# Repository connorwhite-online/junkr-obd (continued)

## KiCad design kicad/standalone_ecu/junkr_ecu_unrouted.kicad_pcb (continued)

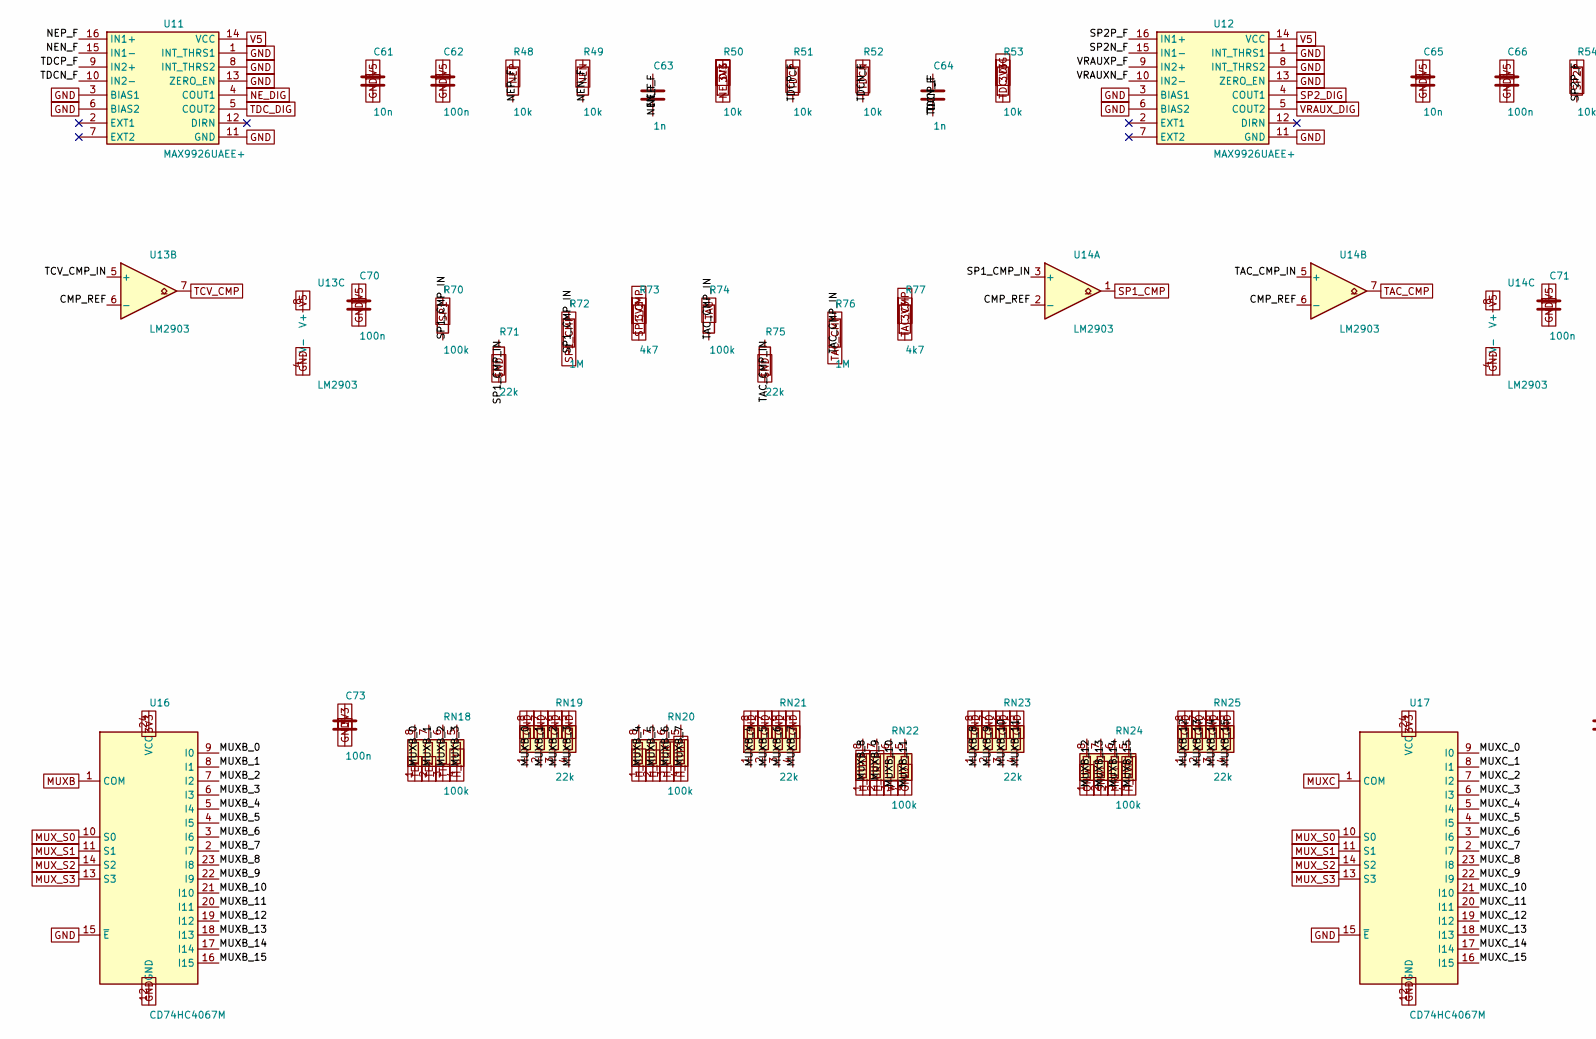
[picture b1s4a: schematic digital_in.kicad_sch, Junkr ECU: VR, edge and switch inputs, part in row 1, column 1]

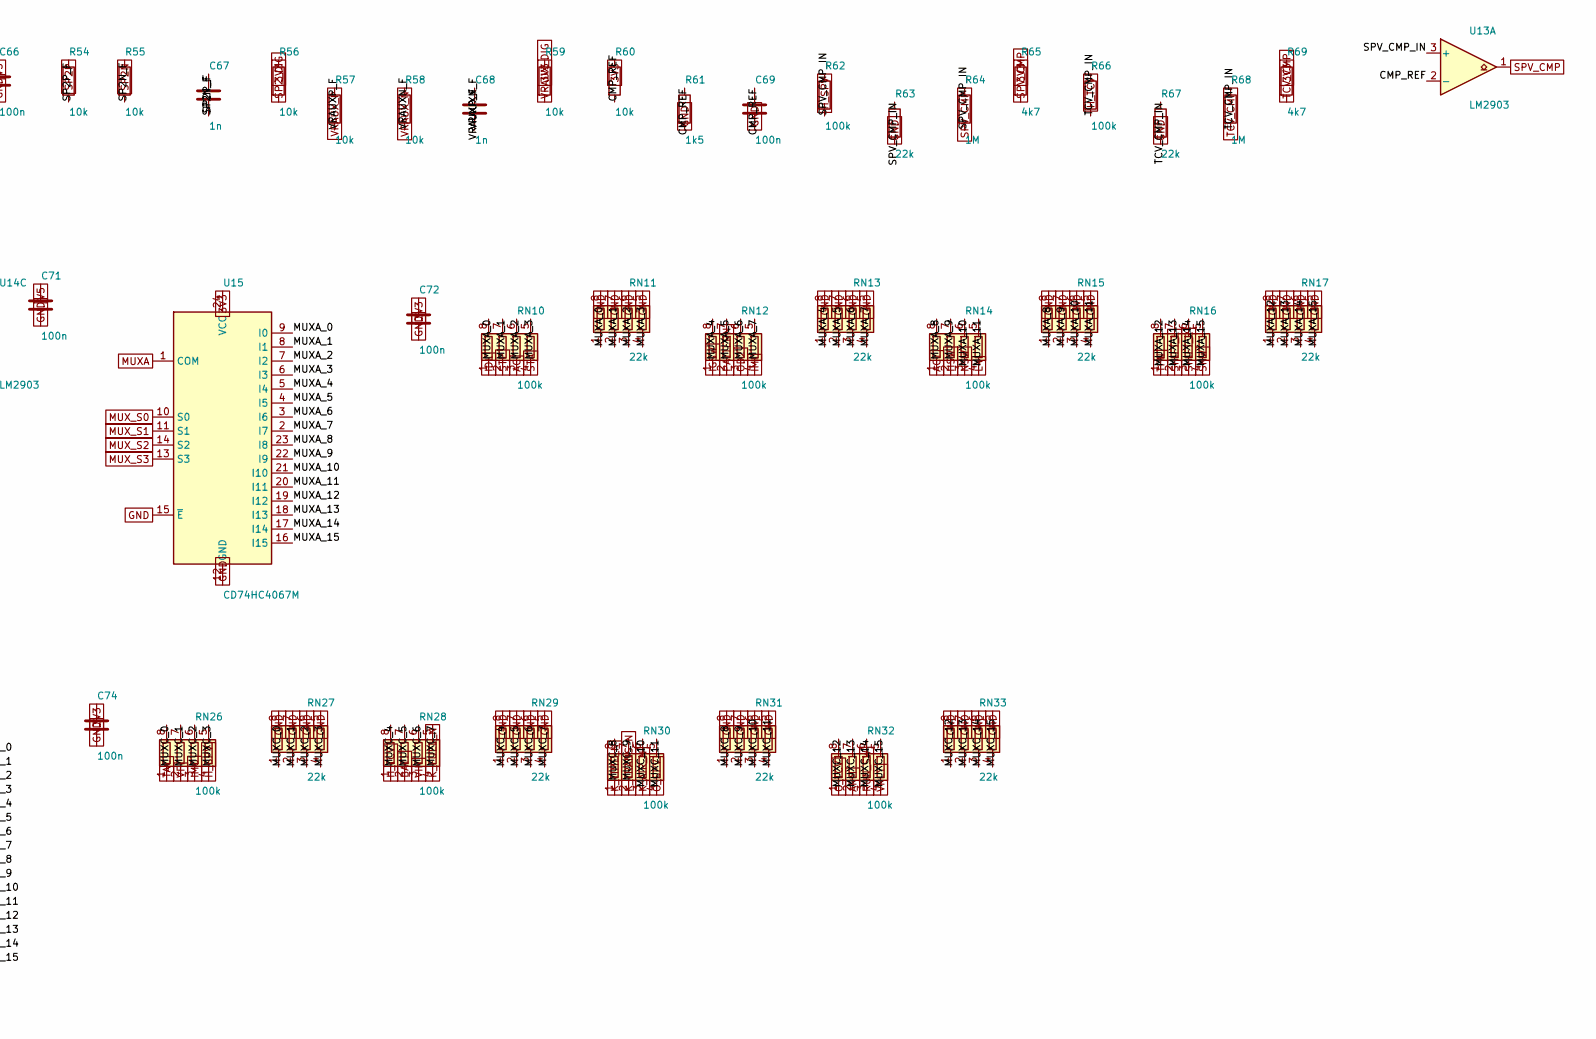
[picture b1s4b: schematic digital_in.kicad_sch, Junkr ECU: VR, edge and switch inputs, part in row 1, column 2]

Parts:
C61, C65: 10n; C_0603_1608Metric
C62, C66, C69, C70, C71, C72, C73, C74: 100n; C_0603_1608Metric
C63, C64, C67, C68: 1n; C_0603_1608Metric
R48, R49, R50, R51, R52, R53, R54, R55, R56, R57, R58, R59, R60: 10k; R_0603_1608Metric
R61: 1k5; R_0603_1608Metric
R62, R66, R70, R74: 100k; R_0603_1608Metric
R63, R67, R71, R75: 22k; R_0603_1608Metric
R64, R68, R72, R76: 1M; R_0603_1608Metric
R65, R69, R73, R77: 4k7; R_0603_1608Metric
RN10, RN12, RN14, RN16, RN18, RN20, RN22, RN24, RN26, RN28, RN30, RN32: 100k; R_Array_Convex_4x0603
RN11, RN13, RN15, RN17, RN19, RN21, RN23, RN25, RN27, RN29, RN31, RN33: 22k; R_Array_Convex_4x0603
U11, U12: MAX9926UAEE+; QSOP-16_3.9x4.9mm_P0.635mm; MPN MAX9926UAEE+
U13, U14: LM2903; SOIC-8_3.9x4.9mm_P1.27mm; MPN LM2903DR
U15, U16, U17: CD74HC4067M; SOIC-24W_7.5x15.4mm_P1.27mm; MPN CD74HC4067M96

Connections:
3V3: C72.1, C73.1, C74.1, R50.1, R53.1, R56.1, R59.1, R60.1, R65.1, R69.1, R73.1, R77.1, U15.24 (VCC), U16.24 (VCC), U17.24 (VCC); also elsewhere on the board
AC: RN10.3 (R3.1); also elsewhere on the board
ACT: RN14.1 (R1.1); also elsewhere on the board
ARM: RN32.2 (R2.1); also elsewhere on the board
BATT: RN28.2 (R2.1); also elsewhere on the board
CMP_REF: C69.1, R60.2, R61.1, U13.2 (-), U13.6 (-), U14.2 (-), U14.6 (-)
GIND: RN22.4 (R4.1); also elsewhere on the board
GND: C61.2, C62.2, C65.2, C66.2, C69.2, C70.2, C71.2, C72.2, C73.2, C74.2, R61.2, R63.2, R67.2, R71.2, R75.2, RN11.5 (R4.2), RN11.6 (R3.2), RN11.7 (R2.2), RN11.8 (R1.2), RN13.5 (R4.2), RN13.6 (R3.2), RN13.7 (R2.2), RN13.8 (R1.2), RN15.5 (R4.2), RN15.6 (R3.2), RN15.7 (R2.2), RN15.8 (R1.2), RN17.5 (R4.2), RN17.6 (R3.2), RN17.7 (R2.2), RN17.8 (R1.2), RN19.5 (R4.2), RN19.6 (R3.2), RN19.7 (R2.2), RN19.8 (R1.2), RN21.5 (R4.2), RN21.6 (R3.2), RN21.7 (R2.2), RN21.8 (R1.2), RN23.5 (R4.2), RN23.6 (R3.2), RN23.7 (R2.2), RN23.8 (R1.2), RN25.5 (R4.2), RN25.6 (R3.2), RN25.7 (R2.2), RN25.8 (R1.2), RN27.5 (R4.2), RN27.6 (R3.2), RN27.7 (R2.2), RN27.8 (R1.2), RN29.5 (R4.2), RN29.6 (R3.2), RN29.7 (R2.2), RN29.8 (R1.2), RN31.5 (R4.2), RN31.6 (R3.2), RN31.7 (R2.2), RN31.8 (R1.2), RN33.5 (R4.2), RN33.6 (R3.2), RN33.7 (R2.2), RN33.8 (R1.2), U11.1 (INT_THRS1), U11.3 (BIAS1), U11.6 (BIAS2), U11.8 (INT_THRS2), U11.11 (GND), U11.13 (ZERO_EN), U12.1 (INT_THRS1), U12.3 (BIAS1), U12.6 (BIAS2), U12.8 (INT_THRS2), U12.11 (GND), U12.13 (ZERO_EN), U13.4 (V-), U14.4 (V-), U15.12 (GND), U15.15 (~E), U16.12 (GND), U16.15 (~E), U17.12 (GND), U17.15 (~E); also elsewhere on the board
HSW: RN14.2 (R2.1); also elsewhere on the board
H_EGR: RN20.3 (R3.1); also elsewhere on the board
H_S1: RN18.4 (R4.1); also elsewhere on the board
H_S2: RN20.1 (R1.1); also elsewhere on the board
H_SL: RN20.2 (R2.1); also elsewhere on the board
H_SPV: R62.1, RN26.4 (R4.1); also elsewhere on the board
H_SREL: RN22.2 (R2.1); also elsewhere on the board
H_STH1: RN20.4 (R4.1); also elsewhere on the board
H_STH2: RN22.1 (R1.1); also elsewhere on the board
H_SVR: RN24.4 (R4.1); also elsewhere on the board
H_TCV: R66.1, RN28.1 (R1.1); also elsewhere on the board
IDL: RN10.1 (R1.1); also elsewhere on the board
IGSW: RN12.1 (R1.1); also elsewhere on the board
IMI: RN12.4 (R4.1); also elsewhere on the board
IMO: RN26.3 (R3.1); also elsewhere on the board
K_AIR_N: RN30.3 (R3.1); also elsewhere on the board
K_FUEL_N: RN28.4 (R4.1); also elsewhere on the board
K_TIME_N: RN30.1 (R1.1); also elsewhere on the board
K_TRANS_N: RN30.2 (R2.1); also elsewhere on the board
L4: RN14.4 (R4.1); also elsewhere on the board
MREL: RN24.3 (R3.1); also elsewhere on the board
MUXA: U15.1 (COM); also elsewhere on the board
MUXA_0: RN10.8 (R1.2), RN11.1 (R1.1), U15.9 (I0)
MUXA_1: RN10.7 (R2.2), RN11.2 (R2.1), U15.8 (I1)
MUXA_2: RN10.6 (R3.2), RN11.3 (R3.1), U15.7 (I2)
MUXA_3: RN10.5 (R4.2), RN11.4 (R4.1), U15.6 (I3)
MUXA_4: RN12.8 (R1.2), RN13.1 (R1.1), U15.5 (I4)
MUXA_5: RN12.7 (R2.2), RN13.2 (R2.1), U15.4 (I5)
MUXA_6: RN12.6 (R3.2), RN13.3 (R3.1), U15.3 (I6)
MUXA_7: RN12.5 (R4.2), RN13.4 (R4.1), U15.2 (I7)
MUXA_8: RN14.8 (R1.2), RN15.1 (R1.1), U15.23 (I8)
MUXA_9: RN14.7 (R2.2), RN15.2 (R2.1), U15.22 (I9)
MUXA_10: RN14.6 (R3.2), RN15.3 (R3.1), U15.21 (I10)
MUXA_11: RN14.5 (R4.2), RN15.4 (R4.1), U15.20 (I11)
MUXA_12: RN16.8 (R1.2), RN17.1 (R1.1), U15.19 (I12)
MUXA_13: RN16.7 (R2.2), RN17.2 (R2.1), U15.18 (I13)
MUXA_14: RN16.6 (R3.2), RN17.3 (R3.1), U15.17 (I14)
MUXA_15: RN16.5 (R4.2), RN17.4 (R4.1), U15.16 (I15)
MUXB: U16.1 (COM); also elsewhere on the board
MUXB_0: RN18.8 (R1.2), RN19.1 (R1.1), U16.9 (I0)
MUXB_1: RN18.7 (R2.2), RN19.2 (R2.1), U16.8 (I1)
MUXB_2: RN18.6 (R3.2), RN19.3 (R3.1), U16.7 (I2)
MUXB_3: RN18.5 (R4.2), RN19.4 (R4.1), U16.6 (I3)
MUXB_4: RN20.8 (R1.2), RN21.1 (R1.1), U16.5 (I4)
MUXB_5: RN20.7 (R2.2), RN21.2 (R2.1), U16.4 (I5)
MUXB_6: RN20.6 (R3.2), RN21.3 (R3.1), U16.3 (I6)
MUXB_7: RN20.5 (R4.2), RN21.4 (R4.1), U16.2 (I7)
MUXB_8: RN22.8 (R1.2), RN23.1 (R1.1), U16.23 (I8)
MUXB_9: RN22.7 (R2.2), RN23.2 (R2.1), U16.22 (I9)
MUXB_10: RN22.6 (R3.2), RN23.3 (R3.1), U16.21 (I10)
MUXB_11: RN22.5 (R4.2), RN23.4 (R4.1), U16.20 (I11)
MUXB_12: RN24.8 (R1.2), RN25.1 (R1.1), U16.19 (I12)
MUXB_13: RN24.7 (R2.2), RN25.2 (R2.1), U16.18 (I13)
MUXB_14: RN24.6 (R3.2), RN25.3 (R3.1), U16.17 (I14)
MUXB_15: RN24.5 (R4.2), RN25.4 (R4.1), U16.16 (I15)
MUXC: U17.1 (COM); also elsewhere on the board
MUXC_0: RN26.8 (R1.2), RN27.1 (R1.1), U17.9 (I0)
MUXC_1: RN26.7 (R2.2), RN27.2 (R2.1), U17.8 (I1)
MUXC_2: RN26.6 (R3.2), RN27.3 (R3.1), U17.7 (I2)
MUXC_3: RN26.5 (R4.2), RN27.4 (R4.1), U17.6 (I3)
MUXC_4: RN28.8 (R1.2), RN29.1 (R1.1), U17.5 (I4)
MUXC_5: RN28.7 (R2.2), RN29.2 (R2.1), U17.4 (I5)
MUXC_6: RN28.6 (R3.2), RN29.3 (R3.1), U17.3 (I6)
MUXC_7: RN28.5 (R4.2), RN29.4 (R4.1), U17.2 (I7)
MUXC_8: RN30.8 (R1.2), RN31.1 (R1.1), U17.23 (I8)
MUXC_9: RN30.7 (R2.2), RN31.2 (R2.1), U17.22 (I9)
MUXC_10: RN30.6 (R3.2), RN31.3 (R3.1), U17.21 (I10)
MUXC_11: RN30.5 (R4.2), RN31.4 (R4.1), U17.20 (I11)
MUXC_12: RN32.8 (R1.2), RN33.1 (R1.1), U17.19 (I12)
MUXC_13: RN32.7 (R2.2), RN33.2 (R2.1), U17.18 (I13)
MUXC_14: RN32.6 (R3.2), RN33.3 (R3.1), U17.17 (I14)
MUXC_15: RN32.5 (R4.2), RN33.4 (R4.1), U17.16 (I15)
MUX_S0: U15.10 (S0), U16.10 (S0), U17.10 (S0); also elsewhere on the board
MUX_S1: U15.11 (S1), U16.11 (S1), U17.11 (S1); also elsewhere on the board
MUX_S2: U15.14 (S2), U16.14 (S2), U17.14 (S2); also elsewhere on the board
MUX_S3: U15.13 (S3), U16.13 (S3), U17.13 (S3); also elsewhere on the board
NEN: R49.1; also elsewhere on the board
NEN_F: C63.2, R49.2, U11.15 (IN1-)
NEP: R48.1; also elsewhere on the board
NEP_F: C63.1, R48.2, U11.16 (IN1+)
NE_DIG: R50.2, U11.4 (COUT1); also elsewhere on the board
NSW: RN14.3 (R3.1); also elsewhere on the board
OD2: RN12.3 (R3.1); also elsewhere on the board
OILW: RN24.1 (R1.1); also elsewhere on the board
O_SPV: RN30.4 (R4.1); also elsewhere on the board
O_TCV: RN32.1 (R1.1); also elsewhere on the board
PATTERN: RN12.2 (R2.1); also elsewhere on the board
RUN_SW: RN32.3 (R3.1); also elsewhere on the board
SHIFT_2: RN16.3 (R3.1); also elsewhere on the board
SHIFT_L: RN16.2 (R2.1); also elsewhere on the board
SNW: RN16.4 (R4.1); also elsewhere on the board
SNWL: RN24.2 (R2.1); also elsewhere on the board
SP1: R70.1; also elsewhere on the board
SP1_CMP: R72.1, R73.2, U14.1; also elsewhere on the board
SP1_CMP_IN: R70.2, R71.1, R72.2, U14.3 (+)
SP2N: R55.1; also elsewhere on the board
SP2N_F: C67.2, R55.2, U12.15 (IN1-)
SP2P: R54.1; also elsewhere on the board
SP2P_F: C67.1, R54.2, U12.16 (IN1+)
SP2_DIG: R56.2, U12.4 (COUT1); also elsewhere on the board
SPV_CMP: R64.1, R65.2, U13.1; also elsewhere on the board
SPV_CMP_IN: R62.2, R63.1, R64.2, U13.3 (+)
STA: RN10.4 (R4.1); also elsewhere on the board
STP: RN10.2 (R2.1); also elsewhere on the board
TAC: R74.1, RN26.1 (R1.1); also elsewhere on the board
TAC_CMP: R76.1, R77.2, U14.7; also elsewhere on the board
TAC_CMP_IN: R74.2, R75.1, R76.2, U14.5 (+)
TCV_CMP: R68.1, R69.2, U13.7; also elsewhere on the board
TCV_CMP_IN: R66.2, R67.1, R68.2, U13.5 (+)
TDCN: R52.1; also elsewhere on the board
TDCN_F: C64.2, R52.2, U11.10 (IN2-)
TDCP: R51.1; also elsewhere on the board
TDCP_F: C64.1, R51.2, U11.9 (IN2+)
TDC_DIG: R53.2, U11.5 (COUT2); also elsewhere on the board
TE1: RN18.1 (R1.1); also elsewhere on the board
TE2: RN18.2 (R2.1); also elsewhere on the board
TFN: RN16.1 (R1.1); also elsewhere on the board
TT: RN18.3 (R3.1); also elsewhere on the board
V5: C61.1, C62.1, C65.1, C66.1, C70.1, C71.1, U11.14 (VCC), U12.14 (VCC), U13.8 (V+), U14.8 (V+); also elsewhere on the board
VF: RN26.2 (R2.1); also elsewhere on the board
VIN: RN28.3 (R3.1); also elsewhere on the board
VRAUXN_F: C68.2, R58.2, U12.10 (IN2-)
VRAUXP_F: C68.1, R57.2, U12.9 (IN2+)
VRAUX_DIG: R59.2, U12.5 (COUT2); also elsewhere on the board
VRAUX_N: R58.1; also elsewhere on the board
VRAUX_P: R57.1; also elsewhere on the board
VRLY: RN32.4 (R4.1); also elsewhere on the board
W: RN22.3 (R3.1); also elsewhere on the board

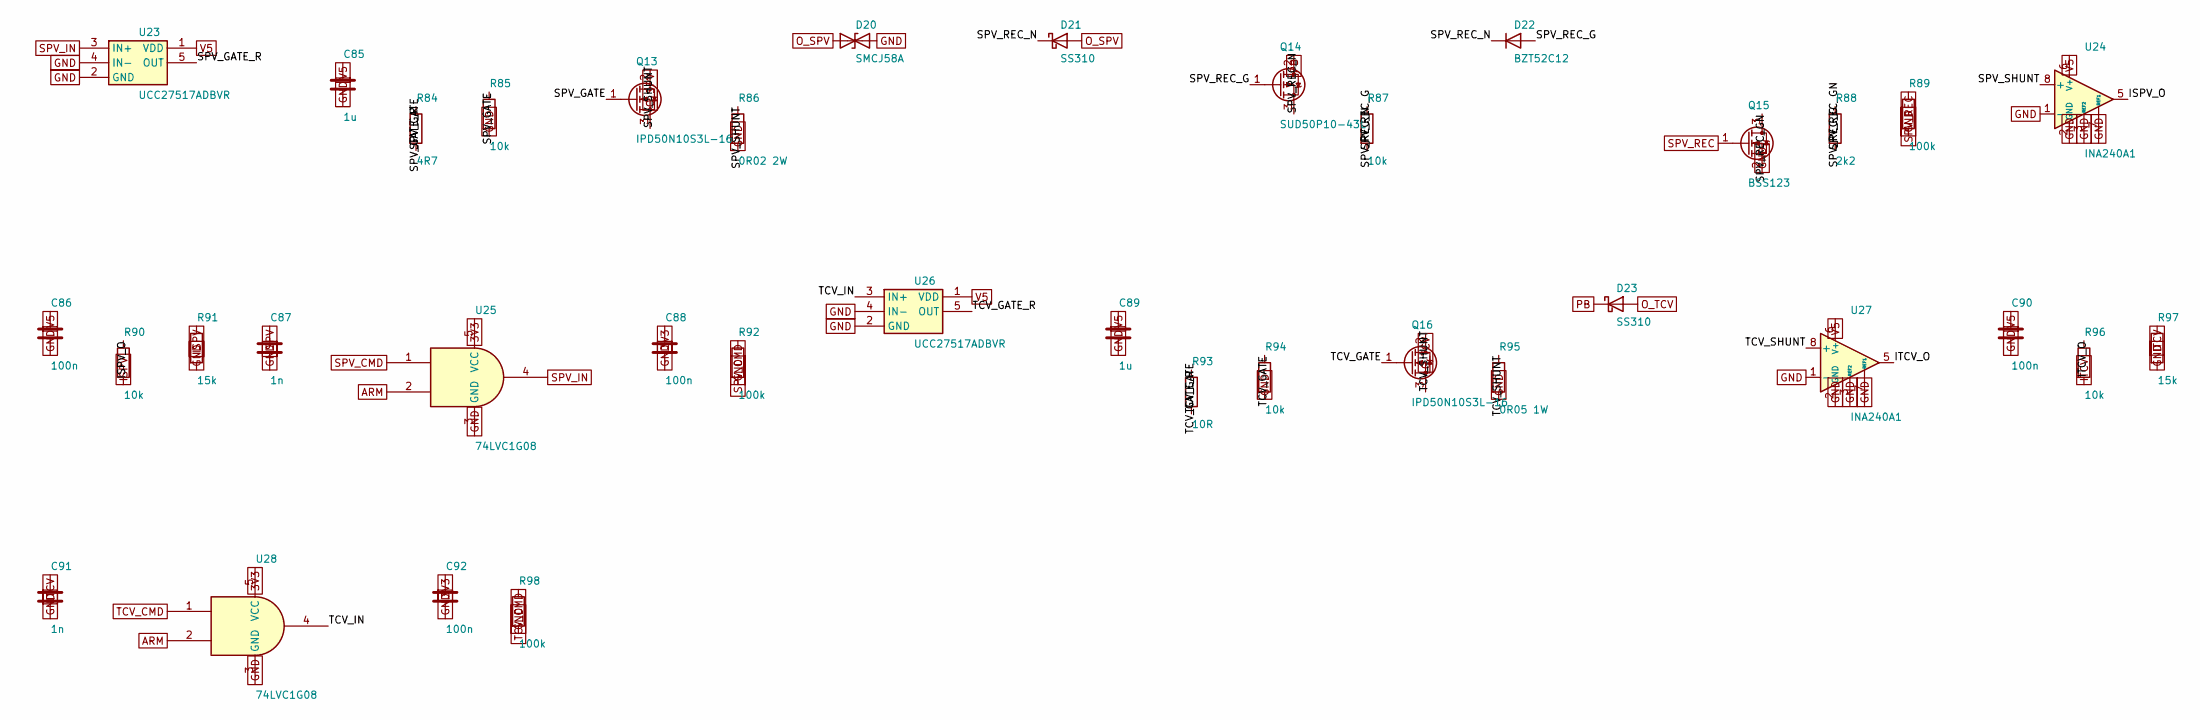
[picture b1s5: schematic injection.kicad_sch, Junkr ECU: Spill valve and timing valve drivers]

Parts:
C85, C89: 1u; C_0603_1608Metric
C86, C88, C90, C92: 100n; C_0603_1608Metric
C87, C91: 1n; C_0603_1608Metric
D20: SMCJ58A; D_SMC; MPN SMCJ58A
D21, D23: SS310; D_SMA; MPN SS310
D22: BZT52C12; D_SOD-123; MPN BZT52C12
Q13, Q16: IPD50N10S3L-16; TO-252-2; MPN IPD50N10S3L16ATMA1
Q14: SUD50P10-43L; TO-252-2; MPN SUD50P10-43L-E3
Q15: BSS123; SOT-23; MPN BSS123
R84: 4R7; R_0603_1608Metric
R85, R87, R90, R94, R96: 10k; R_0603_1608Metric
R86: 0R02 2W; R_2512_6332Metric
R88: 2k2; R_0603_1608Metric
R89, R92, R98: 100k; R_0603_1608Metric
R91, R97: 15k; R_0603_1608Metric
R93: 10R; R_0603_1608Metric
R95: 0R05 1W; R_2512_6332Metric
U23, U26: UCC27517ADBVR; SOT-23-5; MPN UCC27517ADBVR
U24, U27: INA240A1; SOIC-8_3.9x4.9mm_P1.27mm; MPN INA240A1DR
U25, U28: 74LVC1G08; SOT-23-5; MPN SN74LVC1G08DBVR

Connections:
3V3: C88.1, C92.1, U25.5 (VCC), U28.5 (VCC); also elsewhere on the board
ARM: U25.2, U28.2; also elsewhere on the board
GND: C85.2, C86.2, C87.2, C88.2, C89.2, C90.2, C91.2, C92.2, D20.2 (A2), Q15.2 (S), R85.2, R86.2, R89.2, R91.2, R92.2, R94.2, R95.2, R97.2, R98.2, U23.2 (GND), U23.4 (IN-), U24.1 (-), U24.2 (GND), U24.3 (REF2), U24.4 (GND), U24.7 (REF1), U25.3 (GND), U26.2 (GND), U26.4 (IN-), U27.1 (-), U27.2 (GND), U27.3 (REF2), U27.4 (GND), U27.7 (REF1), U28.3 (GND); also elsewhere on the board
ISPV: C87.1, R90.2, R91.1; also elsewhere on the board
ISPV_O: R90.1, U24.5
ITCV: C91.1, R96.2, R97.1; also elsewhere on the board
ITCV_O: R96.1, U27.5
O_SPV: D20.1 (A1), D21.2 (A), Q13.2 (D); also elsewhere on the board
O_TCV: D23.2 (A), Q16.2 (D); also elsewhere on the board
PB: D23.1 (K), Q14.2 (D); also elsewhere on the board
SPV_CMD: R92.1, U25.1; also elsewhere on the board
SPV_GATE: Q13.1 (G), R84.2, R85.1
SPV_GATE_R: R84.1, U23.5 (OUT)
SPV_IN: U23.3 (IN+), U25.4; also elsewhere on the board
SPV_REC: Q15.1 (G), R89.1; also elsewhere on the board
SPV_REC_G: D22.2 (A), Q14.1 (G), R87.2, R88.1
SPV_REC_GN: Q15.3 (D), R88.2
SPV_REC_N: D21.1 (K), D22.1 (K), Q14.3 (S), R87.1
SPV_SHUNT: Q13.3 (S), R86.1, U24.8 (+)
TCV_CMD: R98.1, U28.1; also elsewhere on the board
TCV_GATE: Q16.1 (G), R93.2, R94.1
TCV_GATE_R: R93.1, U26.5 (OUT)
TCV_IN: U26.3 (IN+), U28.4
TCV_SHUNT: Q16.3 (S), R95.1, U27.8 (+)
V5: C85.1, C86.1, C89.1, C90.1, U23.1 (VDD), U24.6 (V+), U26.1 (VDD), U27.6 (V+); also elsewhere on the board

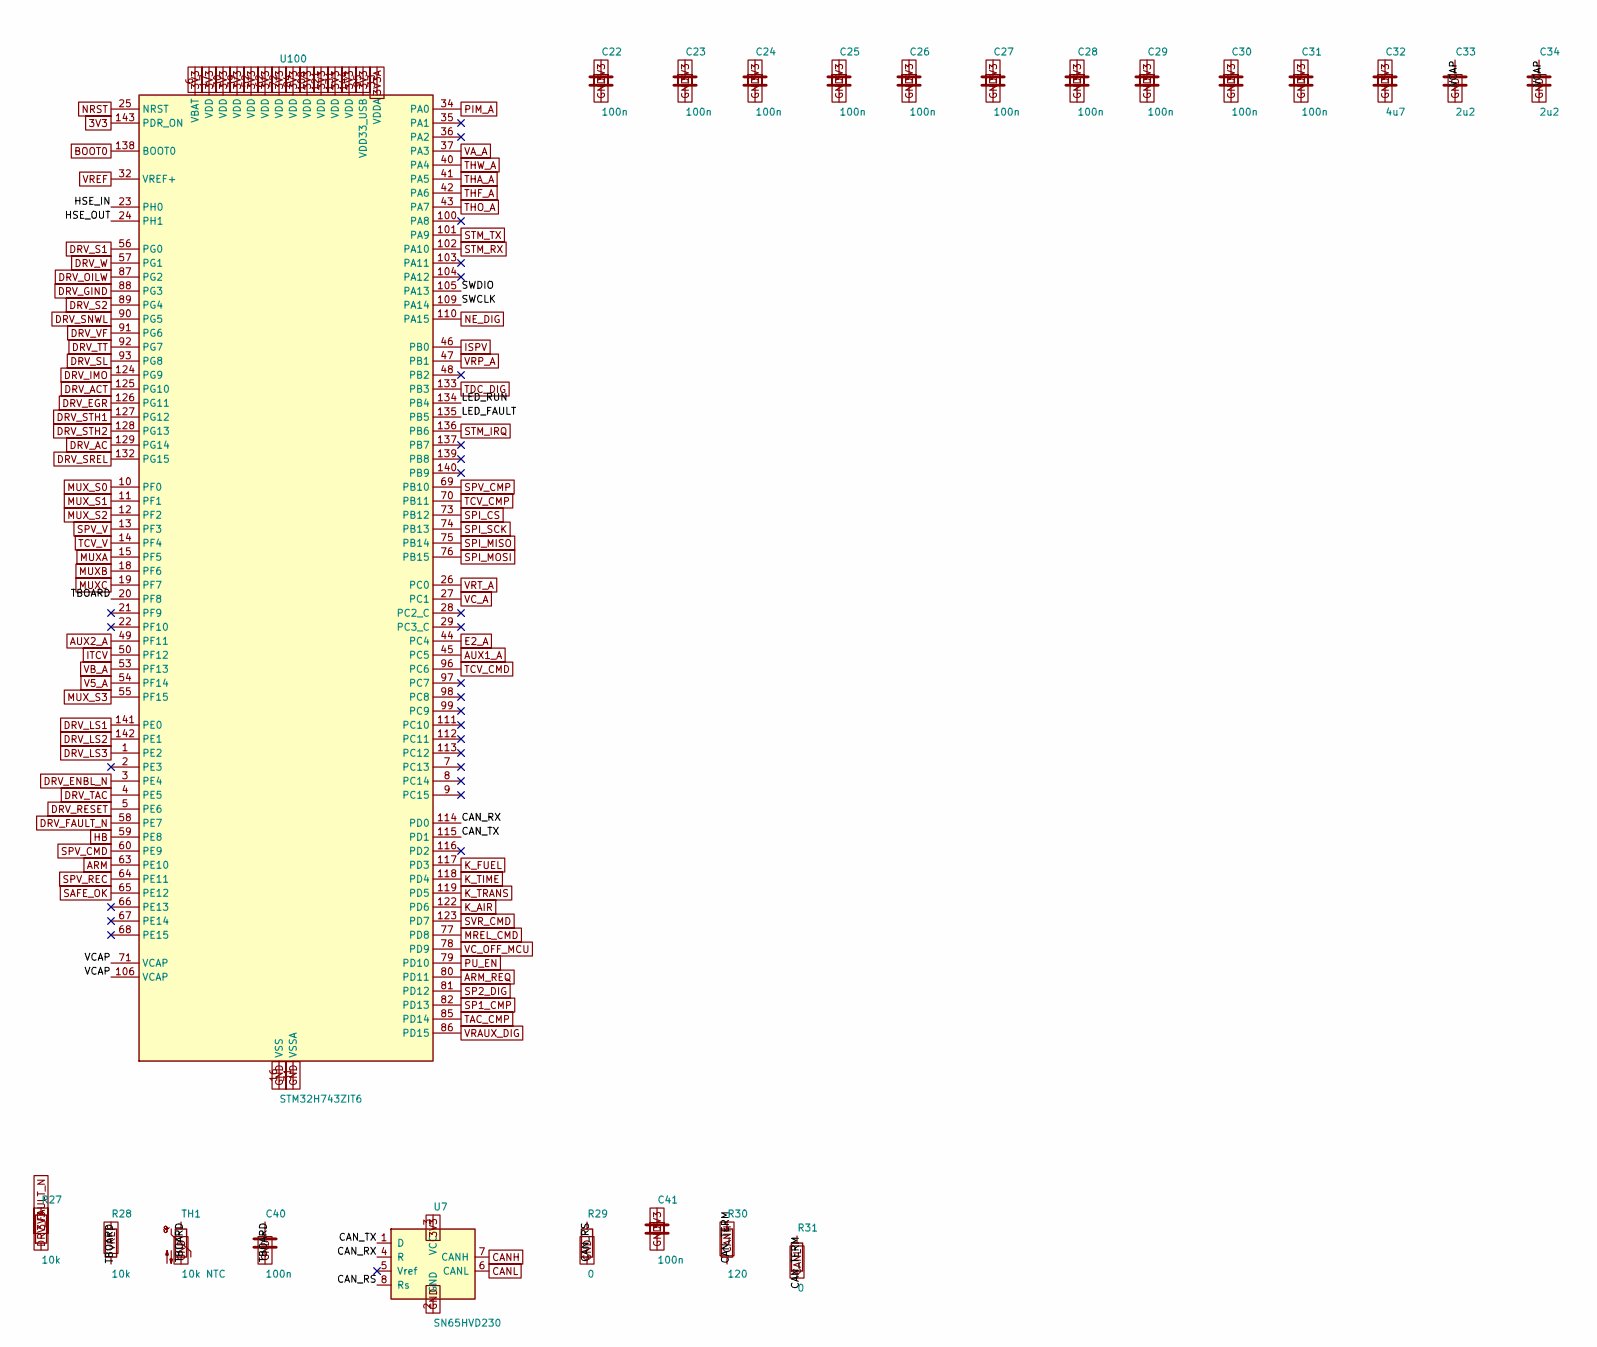
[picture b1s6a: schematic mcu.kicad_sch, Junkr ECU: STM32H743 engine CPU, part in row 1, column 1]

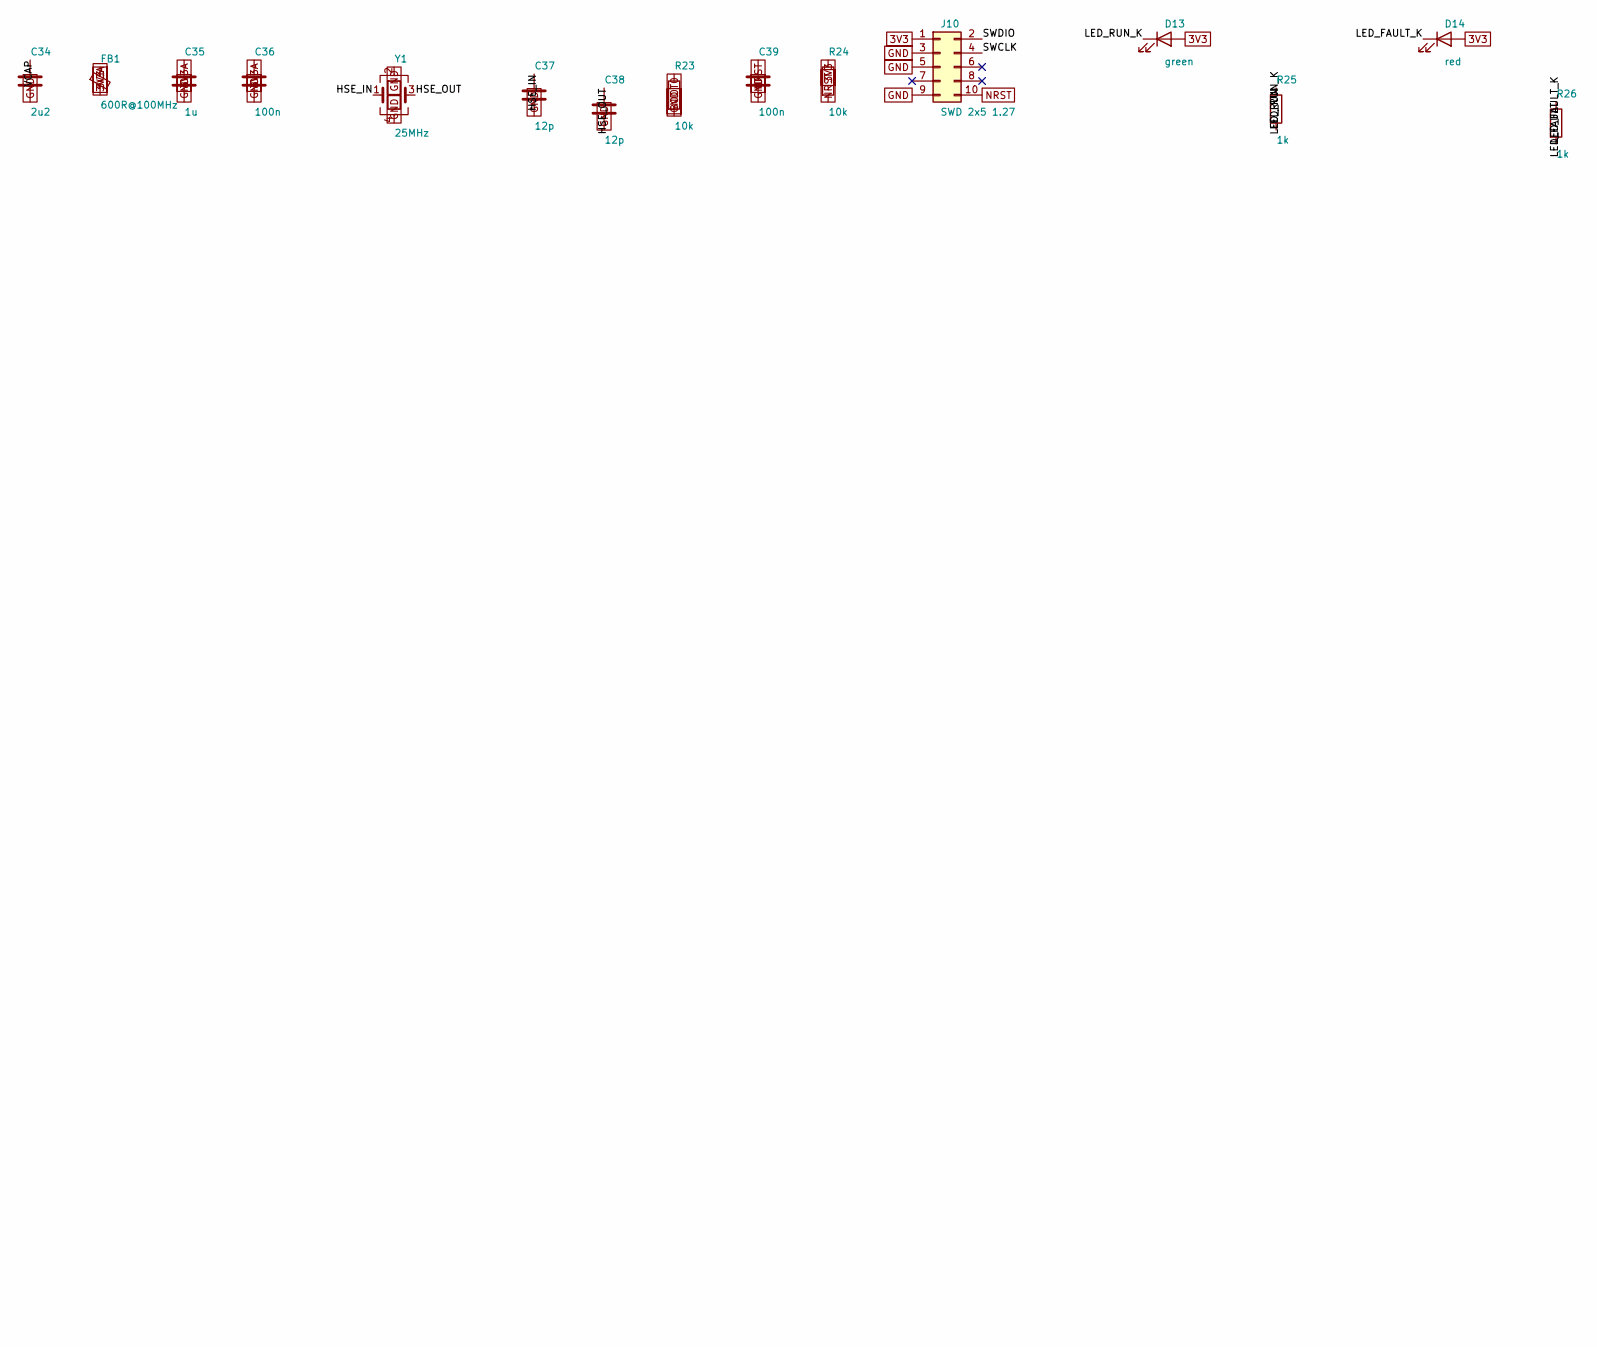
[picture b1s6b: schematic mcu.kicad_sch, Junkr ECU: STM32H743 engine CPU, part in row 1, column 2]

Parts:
C22, C23, C24, C25, C26, C27, C28, C29, C30, C31, C36, C39, C40, C41: 100n; C_0603_1608Metric
C32: 4u7; C_0805_2012Metric
C33, C34: 2u2; C_0603_1608Metric
C35: 1u; C_0603_1608Metric
C37, C38: 12p; C_0603_1608Metric
D13: green; LED_0603_1608Metric
D14: red; LED_0603_1608Metric
FB1: 600R@100MHz; L_0603_1608Metric
J10: SWD 2x5 1.27; PinHeader_2x05_P1.27mm_Vertical_SMD; MPN FTSH-105-01-F-DV-K
R23, R24, R27, R28: 10k; R_0603_1608Metric
R25, R26: 1k; R_0603_1608Metric
R29, R31: 0; R_0603_1608Metric
R30: 120; R_0603_1608Metric
TH1: 10k NTC; R_0603_1608Metric; MPN NCP18XH103F03RB
U7: SN65HVD230; SOIC-8_3.9x4.9mm_P1.27mm; MPN SN65HVD230DR
U100: STM32H743ZIT6; LQFP-144_20x20mm_P0.5mm; MPN STM32H743ZIT6
Y1: 25MHz; Crystal_SMD_3225-4Pin_3.2x2.5mm; MPN ABM8-25.000MHZ-B2-T

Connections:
3V3: C22.1, C23.1, C24.1, C25.1, C26.1, C27.1, C28.1, C29.1, C30.1, C31.1, C32.1, C41.1, D13.2 (A), D14.2 (A), FB1.1, J10.1, R24.1, R27.1, U7.3 (VCC), U100.6 (VBAT), U100.17 (VDD), U100.30 (VDD), U100.39 (VDD), U100.52 (VDD), U100.62 (VDD), U100.72 (VDD), U100.84 (VDD), U100.95 (VDD33_USB), U100.108 (VDD), U100.121 (VDD), U100.131 (VDD), U100.143 (PDR_ON), U100.144 (VDD); also elsewhere on the board
3V3A: C35.1, C36.1, FB1.2, U100.33 (VDDA)
ARM: U100.63 (PE10); also elsewhere on the board
ARM_REQ: U100.80 (PD11); also elsewhere on the board
AUX1_A: U100.45 (PC5); also elsewhere on the board
AUX2_A: U100.49 (PF11); also elsewhere on the board
BOOT0: R23.1, U100.138 (BOOT0); also elsewhere on the board
CANH: R30.1, U7.7 (CANH); also elsewhere on the board
CANL: R31.2, U7.6 (CANL); also elsewhere on the board
CAN_RS: R29.1, U7.8 (Rs)
CAN_RX: U7.4 (R), U100.114 (PD0)
CAN_TERM: R30.2, R31.1
CAN_TX: U7.1 (D), U100.115 (PD1)
DRV_AC: U100.129 (PG14); also elsewhere on the board
DRV_ACT: U100.125 (PG10); also elsewhere on the board
DRV_EGR: U100.126 (PG11); also elsewhere on the board
DRV_ENBL_N: U100.3 (PE4); also elsewhere on the board
DRV_FAULT_N: R27.2, U100.58 (PE7); also elsewhere on the board
DRV_GIND: U100.88 (PG3); also elsewhere on the board
DRV_IMO: U100.124 (PG9); also elsewhere on the board
DRV_LS1: U100.141 (PE0); also elsewhere on the board
DRV_LS2: U100.142 (PE1); also elsewhere on the board
DRV_LS3: U100.1 (PE2); also elsewhere on the board
DRV_OILW: U100.87 (PG2); also elsewhere on the board
DRV_RESET: U100.5 (PE6); also elsewhere on the board
DRV_S1: U100.56 (PG0); also elsewhere on the board
DRV_S2: U100.89 (PG4); also elsewhere on the board
DRV_SL: U100.93 (PG8); also elsewhere on the board
DRV_SNWL: U100.90 (PG5); also elsewhere on the board
DRV_SREL: U100.132 (PG15); also elsewhere on the board
DRV_STH1: U100.127 (PG12); also elsewhere on the board
DRV_STH2: U100.128 (PG13); also elsewhere on the board
DRV_TAC: U100.4 (PE5); also elsewhere on the board
DRV_TT: U100.92 (PG7); also elsewhere on the board
DRV_VF: U100.91 (PG6); also elsewhere on the board
DRV_W: U100.57 (PG1); also elsewhere on the board
E2_A: U100.44 (PC4); also elsewhere on the board
GND: C22.2, C23.2, C24.2, C25.2, C26.2, C27.2, C28.2, C29.2, C30.2, C31.2, C32.2, C33.2, C34.2, C35.2, C36.2, C37.2, C38.2, C39.2, C40.2, C41.2, J10.3, J10.5, J10.9, R23.2, R29.2, TH1.2, U7.2 (GND), U100.16 (VSS), U100.31 (VSSA), U100.38 (VSS), U100.51 (VSS), U100.61 (VSS), U100.83 (VSS), U100.94 (VSS), U100.107 (VSS), U100.120 (VSS), U100.130 (VSS), Y1.2, Y1.4; also elsewhere on the board
HB: U100.59 (PE8); also elsewhere on the board
HSE_IN: C37.1, U100.23 (PH0), Y1.1
HSE_OUT: C38.1, U100.24 (PH1), Y1.3
ISPV: U100.46 (PB0); also elsewhere on the board
ITCV: U100.50 (PF12); also elsewhere on the board
K_AIR: U100.122 (PD6); also elsewhere on the board
K_FUEL: U100.117 (PD3); also elsewhere on the board
K_TIME: U100.118 (PD4); also elsewhere on the board
K_TRANS: U100.119 (PD5); also elsewhere on the board
LED_FAULT: R26.1, U100.135 (PB5)
LED_FAULT_K: D14.1 (K), R26.2
LED_RUN: R25.1, U100.134 (PB4)
LED_RUN_K: D13.1 (K), R25.2
MREL_CMD: U100.77 (PD8); also elsewhere on the board
MUXA: U100.15 (PF5); also elsewhere on the board
MUXB: U100.18 (PF6); also elsewhere on the board
MUXC: U100.19 (PF7); also elsewhere on the board
MUX_S0: U100.10 (PF0); also elsewhere on the board
MUX_S1: U100.11 (PF1); also elsewhere on the board
MUX_S2: U100.12 (PF2); also elsewhere on the board
MUX_S3: U100.55 (PF15); also elsewhere on the board
NE_DIG: U100.110 (PA15); also elsewhere on the board
NRST: C39.1, J10.10, R24.2, U100.25 (NRST); also elsewhere on the board
PIM_A: U100.34 (PA0); also elsewhere on the board
PU_EN: U100.79 (PD10); also elsewhere on the board
SAFE_OK: U100.65 (PE12); also elsewhere on the board
SP1_CMP: U100.82 (PD13); also elsewhere on the board
SP2_DIG: U100.81 (PD12); also elsewhere on the board
SPI_CS: U100.73 (PB12); also elsewhere on the board
SPI_MISO: U100.75 (PB14); also elsewhere on the board
SPI_MOSI: U100.76 (PB15); also elsewhere on the board
SPI_SCK: U100.74 (PB13); also elsewhere on the board
SPV_CMD: U100.60 (PE9); also elsewhere on the board
SPV_CMP: U100.69 (PB10); also elsewhere on the board
SPV_REC: U100.64 (PE11); also elsewhere on the board
SPV_V: U100.13 (PF3); also elsewhere on the board
STM_IRQ: U100.136 (PB6); also elsewhere on the board
STM_RX: U100.102 (PA10); also elsewhere on the board
STM_TX: U100.101 (PA9); also elsewhere on the board
SVR_CMD: U100.123 (PD7); also elsewhere on the board
SWCLK: J10.4, U100.109 (PA14)
SWDIO: J10.2, U100.105 (PA13)
TAC_CMP: U100.85 (PD14); also elsewhere on the board
TBOARD: C40.1, R28.2, TH1.1, U100.20 (PF8)
TCV_CMD: U100.96 (PC6); also elsewhere on the board
TCV_CMP: U100.70 (PB11); also elsewhere on the board
TCV_V: U100.14 (PF4); also elsewhere on the board
TDC_DIG: U100.133 (PB3); also elsewhere on the board
THA_A: U100.41 (PA5); also elsewhere on the board
THF_A: U100.42 (PA6); also elsewhere on the board
THO_A: U100.43 (PA7); also elsewhere on the board
THW_A: U100.40 (PA4); also elsewhere on the board
V5_A: U100.54 (PF14); also elsewhere on the board
VA_A: U100.37 (PA3); also elsewhere on the board
VB_A: U100.53 (PF13); also elsewhere on the board
VCAP: C33.1, C34.1, U100.71 (VCAP), U100.106 (VCAP)
VC_A: U100.27 (PC1); also elsewhere on the board
VC_OFF_MCU: U100.78 (PD9); also elsewhere on the board
VRAUX_DIG: U100.86 (PD15); also elsewhere on the board
VREF: R28.1, U100.32 (VREF+); also elsewhere on the board
VRP_A: U100.47 (PB1); also elsewhere on the board
VRT_A: U100.26 (PC0); also elsewhere on the board
